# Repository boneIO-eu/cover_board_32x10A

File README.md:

# Cover Board 32x10A for 16 shutters (up/down)
This board is discontinued.
It is replaced by cover option in relay board 32x10A.

More info: http://docs.boneio.eu/

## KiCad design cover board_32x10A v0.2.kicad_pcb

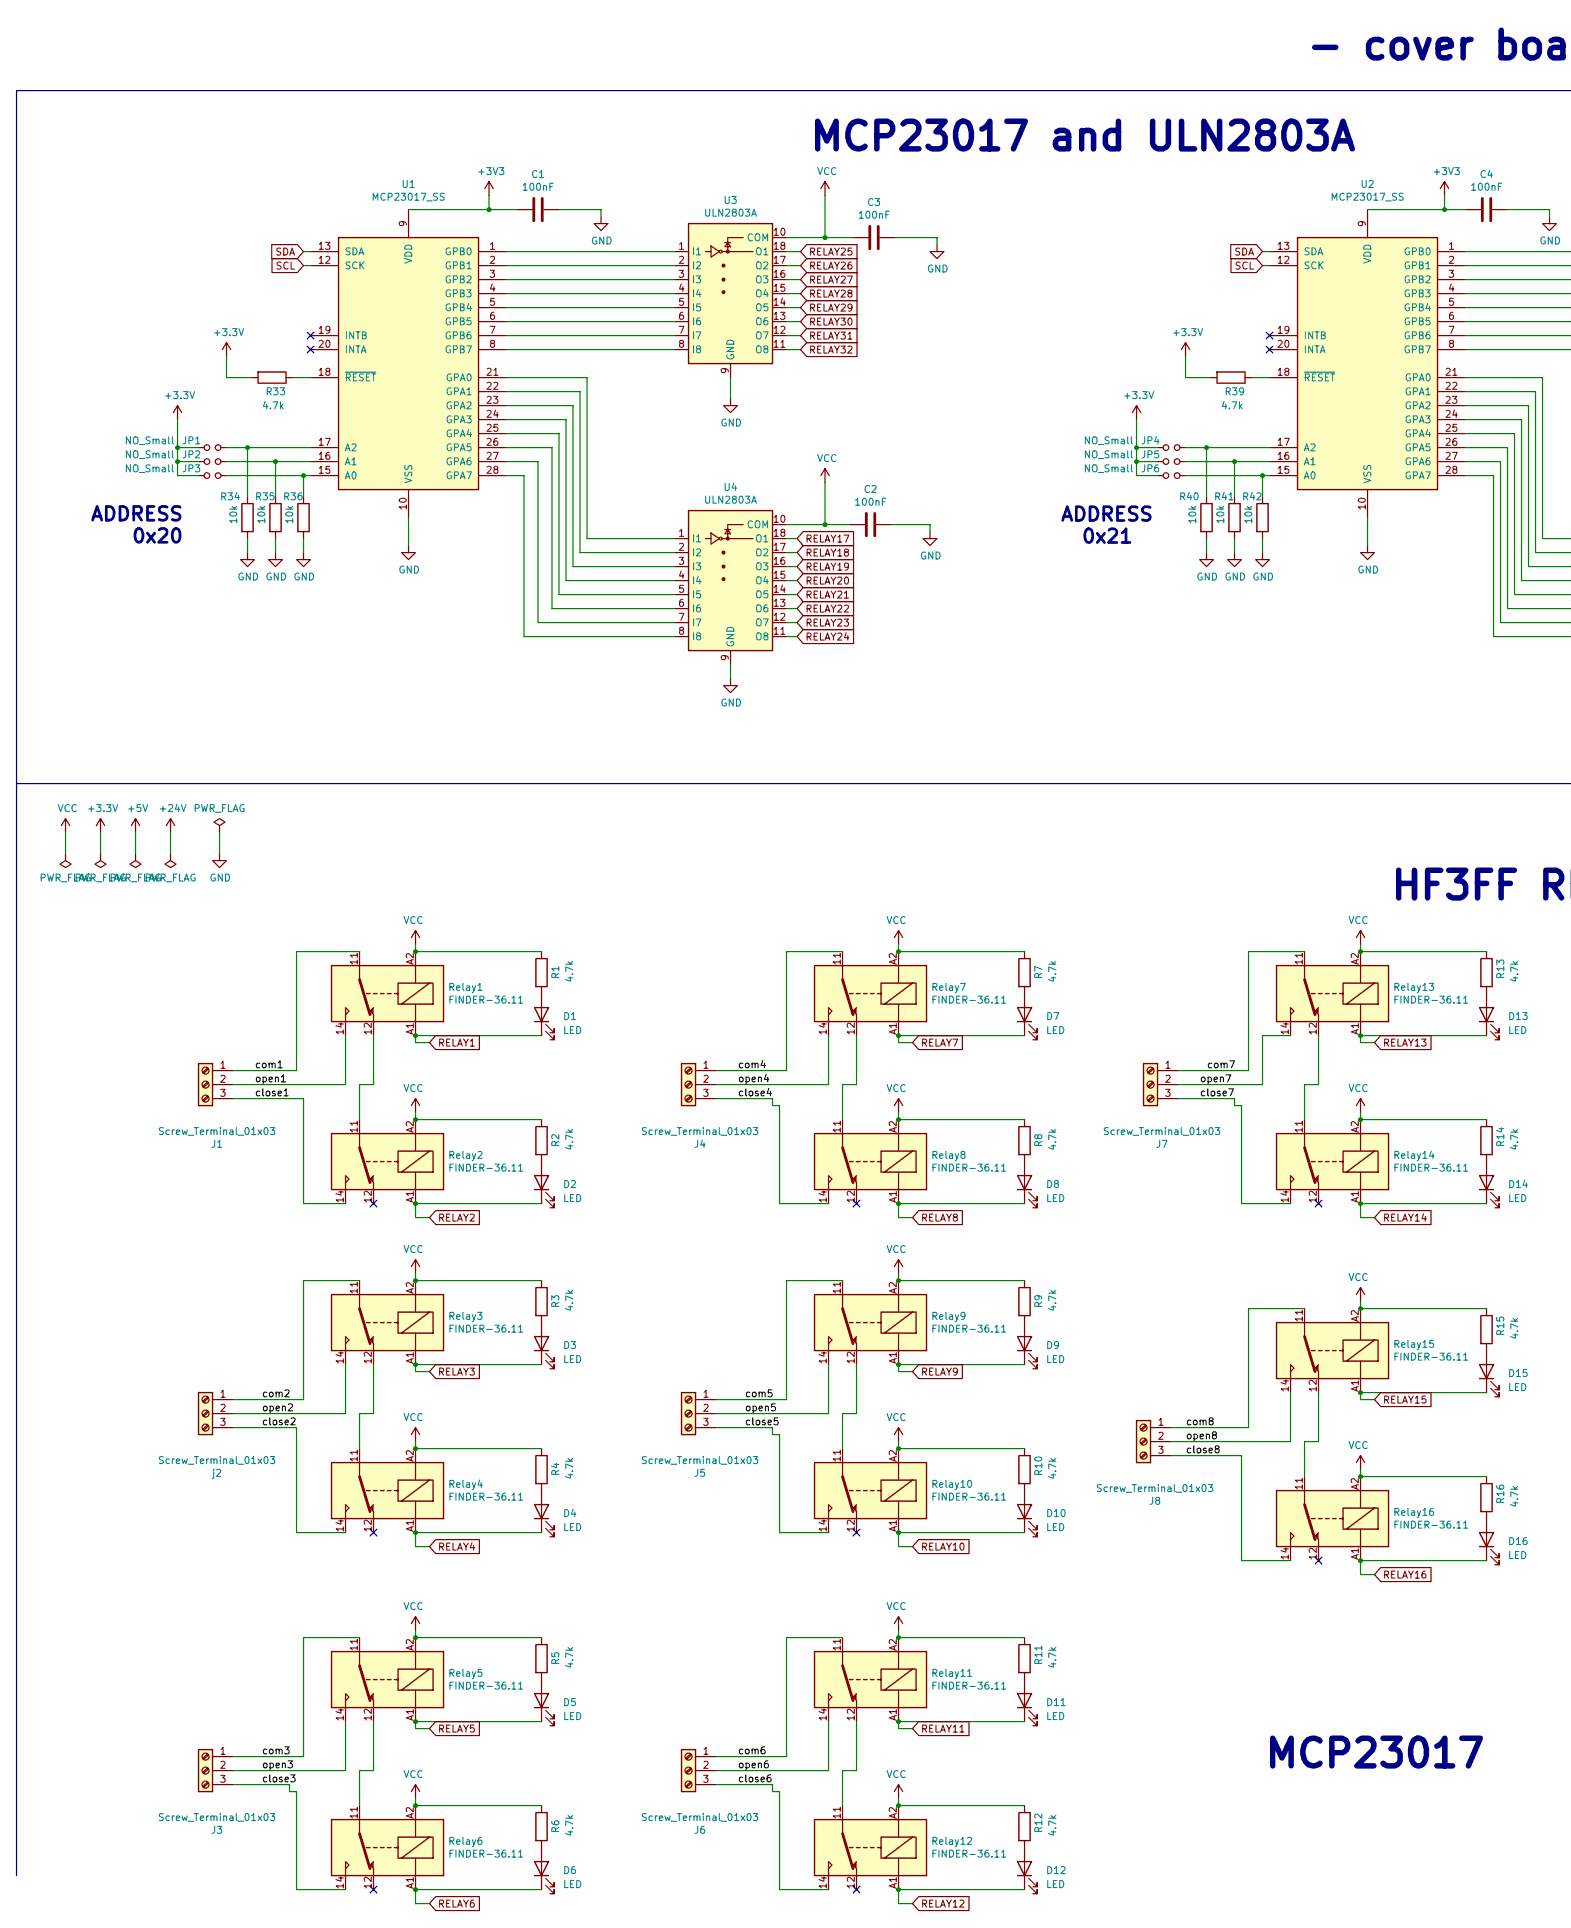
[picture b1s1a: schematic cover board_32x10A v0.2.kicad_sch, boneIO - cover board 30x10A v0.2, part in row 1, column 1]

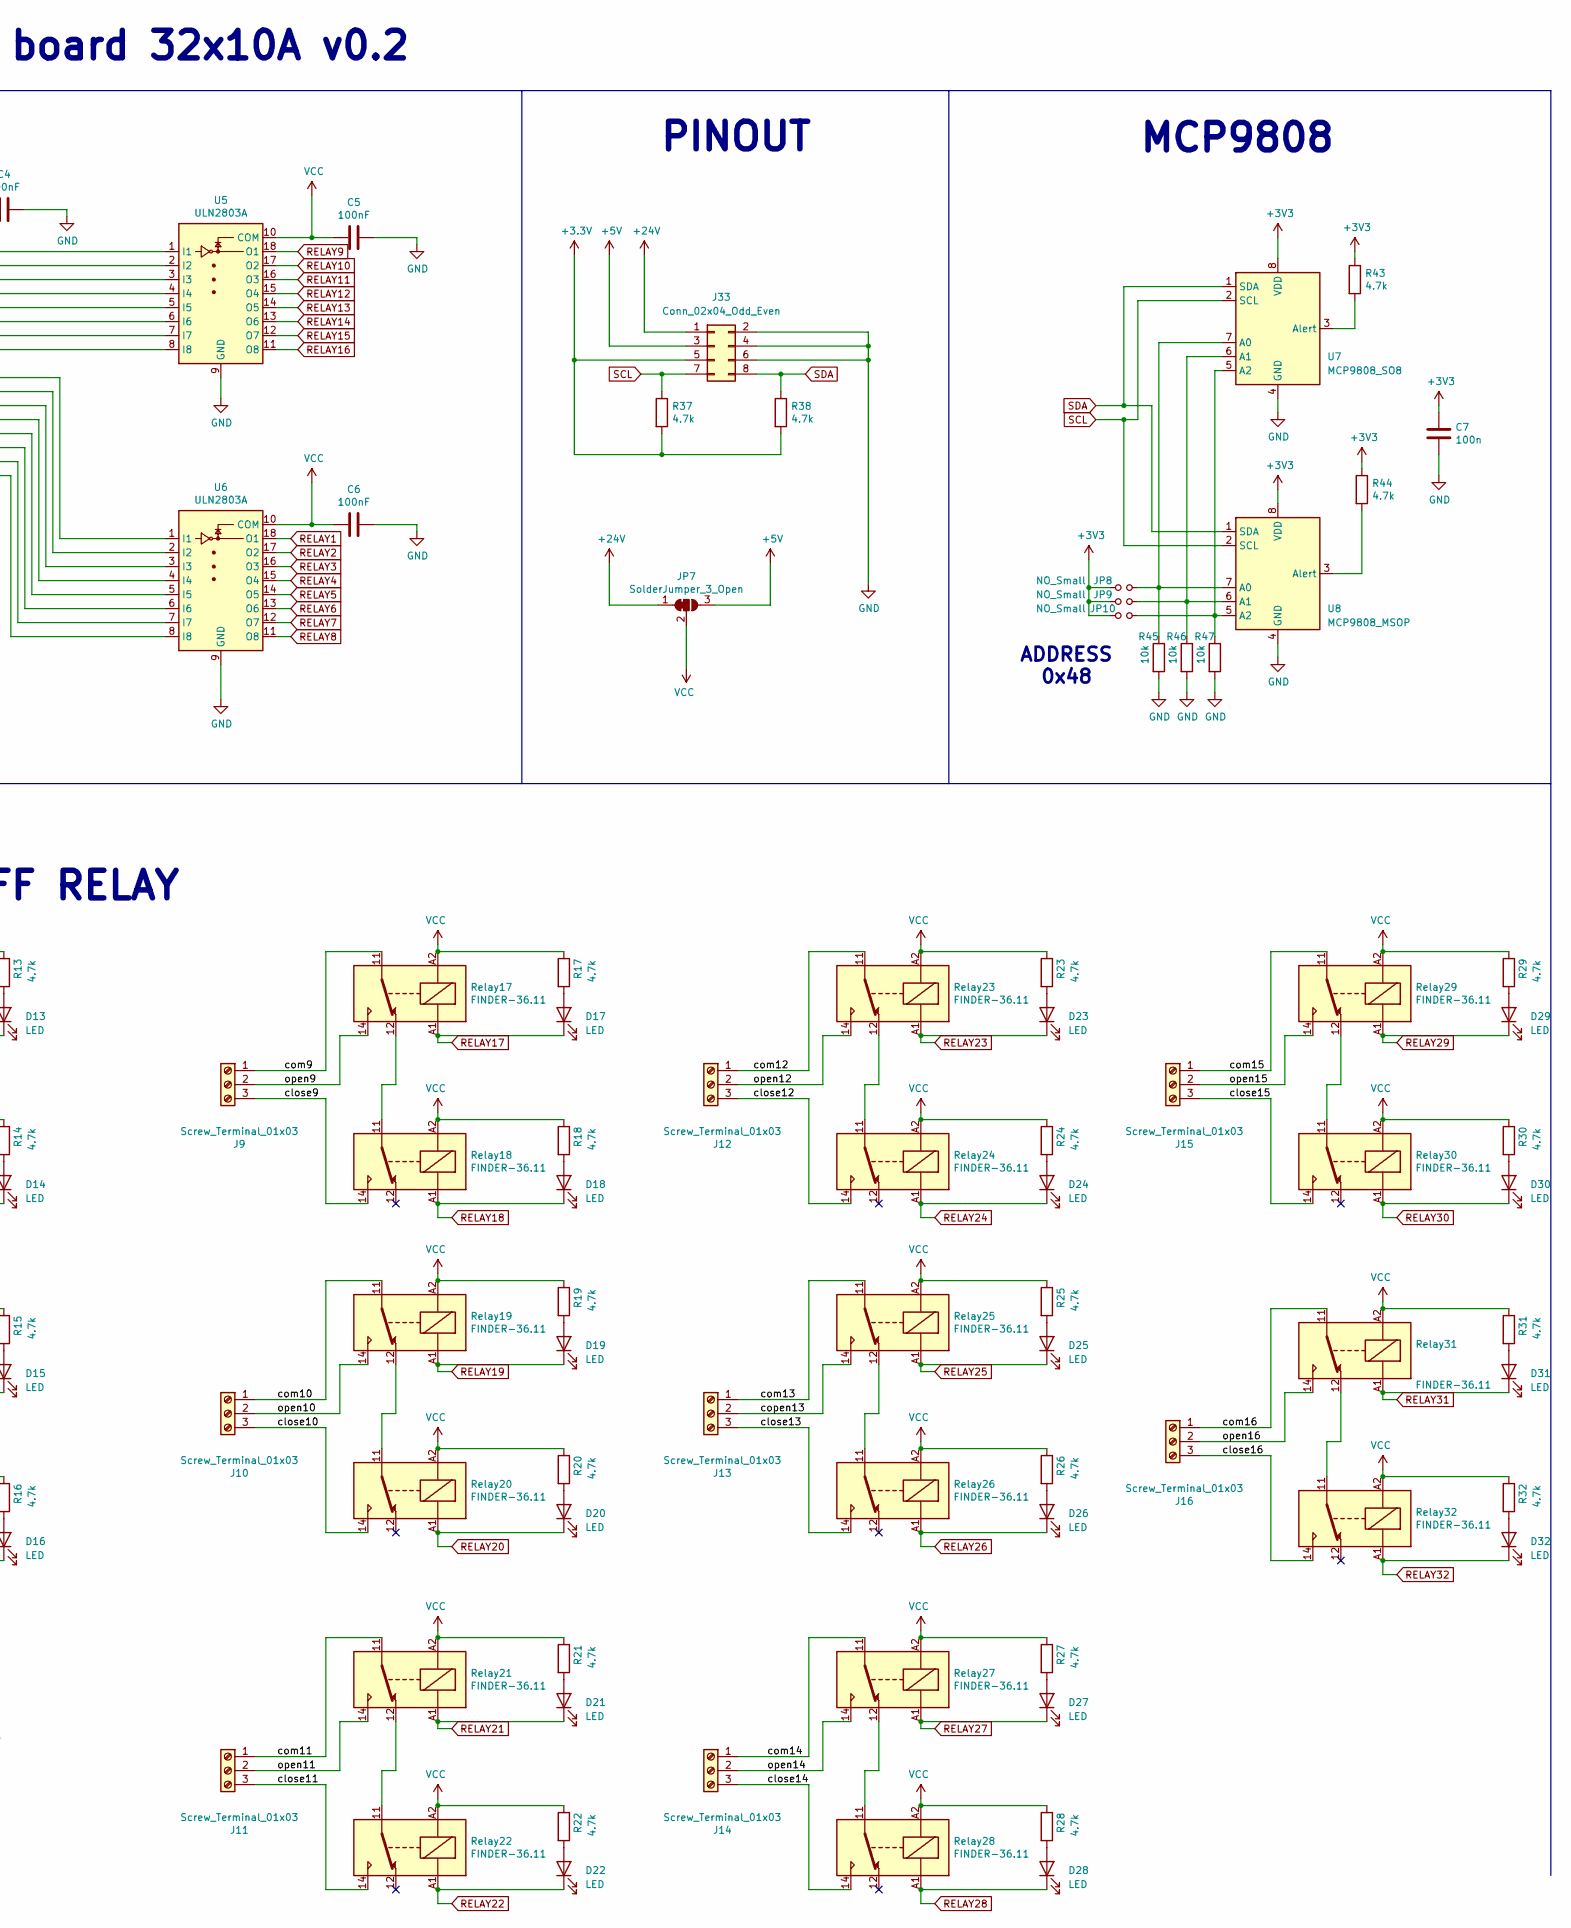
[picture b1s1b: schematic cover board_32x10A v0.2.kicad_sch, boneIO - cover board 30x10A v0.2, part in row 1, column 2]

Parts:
C1, C2, C3, C4, C5, C6: 100nF; C_0603_1608Metric
C7: 100n; C_0603_1608Metric
D1, D2, D3, D4, D5, D6, D7, D8, D9, D10, D11, D12, D13, D14, D15, D16, D17, D18, D19, D20, D21, D22, D23, D24, D25, D26, D27, D28, D29, D30, D31, D32: LED; LED_0603_1608Metric
J1, J3, J4, J5, J6, J7, J8, J9, J10, J11, J12, J13, J14, J15, J16: Screw_Terminal_01x03; PhoenixContact_GMSTBA_2,5_3-G_1x03_P7.50mm_Horizontal
J33: Conn_02x04_Odd_Even; PinHeader_2x04_P2.54mm_Vertical
JP1, JP2, JP3, JP4, JP5, JP6, JP8, JP9, JP10: NO_Small; SolderJumper-2_P1.3mm_Open_RoundedPad1.0x1.5mm
JP7: SolderJumper_3_Open; SolderJumper-3_P1.3mm_Bridged12_RoundedPad1.0x1.5mm
R1, R2, R3, R4, R5, R6, R7, R8, R9, R10, R11, R12, R13, R14, R15, R16, R17, R18, R19, R20, R21, R22, R23, R24, R25, R26, R27, R28, R29, R30, R31, R32, R33, R37, R38, R39, R43, R44: 4.7k; R_0603_1608Metric
R34, R35, R36, R40, R41, R42, R45, R46, R47: 10k; R_0603_1608Metric
Relay1, Relay2, Relay3, Relay4, Relay5, Relay6, Relay7, Relay8, Relay9, Relay10, Relay11, Relay12, Relay13, Relay14, Relay15, Relay16, Relay17, Relay18, Relay19, Relay20, Relay21, Relay22, Relay23, Relay24, Relay25, Relay26, Relay27, Relay28, Relay29, Relay30, Relay31, Relay32: FINDER-36.11; Relay_SPDT_Finder_36.11
U1, U2: MCP23017_SS; SSOP-28_5.3x10.2mm_P0.65mm
U3, U4, U5, U6: ULN2803A; SOIC-18W_7.5x11.6mm_P1.27mm
U7: MCP9808_SO8; SO-8_3.9x4.9mm_P1.27mm
U8: MCP9808_MSOP; MSOP-8_3x3mm_P0.65mm
j2: Screw_Terminal_01x03; PhoenixContact_GMSTBA_2,5_3-G_1x03_P7.50mm_Horizontal

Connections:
+5V: J33.3, JP7.3 (B)
+24V: J33.1, JP7.1 (A)
/close1: J1.3, Relay2.14
/close2: Relay4.14, j2.3
/close3: J3.3, Relay6.14
/close4: J4.3, Relay8.14
/close5: J5.3, Relay10.14
/close6: J6.3, Relay12.14
/close7: J7.3, Relay14.14
/close8: J8.3, Relay16.14
/close9: J9.3, Relay18.14
/close10: J10.3, Relay20.14
/close11: J11.3, Relay22.14
/close12: J12.3, Relay24.14
/close13: J13.3, Relay26.14
/close14: J14.3, Relay28.14
/close15: J15.3, Relay30.14
/close16: J16.3, Relay32.14
/com1: J1.1, Relay1.11
/com2: Relay3.11, j2.1
/com3: J3.1, Relay5.11
/com4: J4.1, Relay7.11
/com5: J5.1, Relay9.11
/com6: J6.1, Relay11.11
/com7: J7.1, Relay13.11
/com8: J8.1, Relay15.11
/com9: J9.1, Relay17.11
/com10: J10.1, Relay19.11
/com11: J11.1, Relay21.11
/com12: J12.1, Relay23.11
/com13: J13.1, Relay25.11
/com14: J14.1, Relay27.11
/com15: J15.1, Relay29.11
/com16: J16.1, Relay31.11
/copen13: J13.2, Relay25.14
/open1: J1.2, Relay1.14
/open2: Relay3.14, j2.2
/open3: J3.2, Relay5.14
/open4: J4.2, Relay7.14
/open5: J5.2, Relay9.14
/open6: J6.2, Relay11.14
/open7: J7.2, Relay13.14
/open8: J8.2, Relay15.14
/open9: J9.2, Relay17.14
/open10: J10.2, Relay19.14
/open11: J11.2, Relay21.14
/open12: J12.2, Relay23.14
/open14: J14.2, Relay27.14
/open15: J15.2, Relay29.14
/open16: J16.2, Relay31.14
GND: C1.1, C2.1, C3.1, C4.1, C5.1, C6.1, C7.2, J33.2, J33.4, J33.6, R34.2, R35.2, R36.2, R40.2, R41.2, R42.2, R45.2, R46.2, R47.2, U1.10 (VSS), U2.10 (VSS), U3.9 (GND), U4.9 (GND), U5.9 (GND), U6.9 (GND), U7.4 (GND), U8.4 (GND)
unnamed: D1.2 (A), R1.2
unnamed: D2.2 (A), R2.2
unnamed: D3.2 (A), R3.2
unnamed: D4.2 (A), R4.2
unnamed: D5.2 (A), R5.2
unnamed: D6.2 (A), R6.2
unnamed: D7.2 (A), R7.2
unnamed: D8.2 (A), R8.2
unnamed: D9.2 (A), R9.2
unnamed: D10.2 (A), R10.2
unnamed: D11.2 (A), R11.2
unnamed: D12.2 (A), R12.2
unnamed: D13.2 (A), R13.2
unnamed: D14.2 (A), R14.2
unnamed: D15.2 (A), R15.2
unnamed: D16.2 (A), R16.2
unnamed: D17.2 (A), R17.2
unnamed: D18.2 (A), R18.2
unnamed: D19.2 (A), R19.2
unnamed: D20.2 (A), R20.2
unnamed: D21.2 (A), R21.2
unnamed: D22.2 (A), R22.2
unnamed: D23.2 (A), R23.2
unnamed: D24.2 (A), R24.2
unnamed: D25.2 (A), R25.2
unnamed: D26.2 (A), R26.2
unnamed: D27.2 (A), R27.2
unnamed: D28.2 (A), R28.2
unnamed: D29.2 (A), R29.2
unnamed: D30.2 (A), R30.2
unnamed: D31.2 (A), R31.2
unnamed: D32.2 (A), R32.2
unnamed: JP1.2, R34.1, U1.17 (A2)
unnamed: JP2.2, R35.1, U1.16 (A1)
unnamed: JP3.2, R36.1, U1.15 (A0)
unnamed: JP4.2, R40.1, U2.17 (A2)
unnamed: JP5.2, R41.1, U2.16 (A1)
unnamed: JP6.2, R42.1, U2.15 (A0)
unnamed: JP8.2, R45.1, U7.7 (A0), U8.7 (A0)
unnamed: JP9.2, R46.1, U7.6 (A1), U8.6 (A1)
unnamed: JP10.2, R47.1, U7.5 (A2), U8.5 (A2)
unnamed: R33.1, U1.18 (~RESET)
unnamed: R39.1, U2.18 (~RESET)
unnamed: R43.2, U7.3 (Alert)
unnamed: R44.2, U8.3 (Alert)
unnamed: Relay1.12, Relay2.11
unnamed: Relay3.12, Relay4.11
unnamed: Relay5.12, Relay6.11
unnamed: Relay7.12, Relay8.11
unnamed: Relay9.12, Relay10.11
unnamed: Relay11.12, Relay12.11
unnamed: Relay13.12, Relay14.11
unnamed: Relay15.12, Relay16.11
unnamed: Relay17.12, Relay18.11
unnamed: Relay19.12, Relay20.11
unnamed: Relay21.12, Relay22.11
unnamed: Relay23.12, Relay24.11
unnamed: Relay25.12, Relay26.11
unnamed: Relay27.12, Relay28.11
unnamed: Relay29.12, Relay30.11
unnamed: Relay31.12, Relay32.11
unnamed: U1.1 (GPB0), U3.1 (I1)
unnamed: U1.2 (GPB1), U3.2 (I2)
unnamed: U1.3 (GPB2), U3.3 (I3)
unnamed: U1.4 (GPB3), U3.4 (I4)
unnamed: U1.5 (GPB4), U3.5 (I5)
unnamed: U1.6 (GPB5), U3.6 (I6)
unnamed: U1.7 (GPB6), U3.7 (I7)
unnamed: U1.8 (GPB7), U3.8 (I8)
unnamed: U1.21 (GPA0), U4.1 (I1)
unnamed: U1.22 (GPA1), U4.2 (I2)
unnamed: U1.23 (GPA2), U4.3 (I3)
unnamed: U1.24 (GPA3), U4.4 (I4)
unnamed: U1.25 (GPA4), U4.5 (I5)
unnamed: U1.26 (GPA5), U4.6 (I6)
unnamed: U1.27 (GPA6), U4.7 (I7)
unnamed: U1.28 (GPA7), U4.8 (I8)
unnamed: U2.1 (GPB0), U5.1 (I1)
unnamed: U2.2 (GPB1), U5.2 (I2)
unnamed: U2.3 (GPB2), U5.3 (I3)
unnamed: U2.4 (GPB3), U5.4 (I4)
unnamed: U2.5 (GPB4), U5.5 (I5)
unnamed: U2.6 (GPB5), U5.6 (I6)
unnamed: U2.7 (GPB6), U5.7 (I7)
unnamed: U2.8 (GPB7), U5.8 (I8)
unnamed: U2.21 (GPA0), U6.1 (I1)
unnamed: U2.22 (GPA1), U6.2 (I2)
unnamed: U2.23 (GPA2), U6.3 (I3)
unnamed: U2.24 (GPA3), U6.4 (I4)
unnamed: U2.25 (GPA4), U6.5 (I5)
unnamed: U2.26 (GPA5), U6.6 (I6)
unnamed: U2.27 (GPA6), U6.7 (I7)
unnamed: U2.28 (GPA7), U6.8 (I8)
RELAY1: D1.1 (K), Relay1.A1, U6.18 (O1)
RELAY2: D2.1 (K), Relay2.A1, U6.17 (O2)
RELAY3: D3.1 (K), Relay3.A1, U6.16 (O3)
RELAY4: D4.1 (K), Relay4.A1, U6.15 (O4)
RELAY5: D5.1 (K), Relay5.A1, U6.14 (O5)
RELAY6: D6.1 (K), Relay6.A1, U6.13 (O6)
RELAY7: D7.1 (K), Relay7.A1, U6.12 (O7)
RELAY8: D8.1 (K), Relay8.A1, U6.11 (O8)
RELAY9: D9.1 (K), Relay9.A1, U5.18 (O1)
RELAY10: D10.1 (K), Relay10.A1, U5.17 (O2)
RELAY11: D11.1 (K), Relay11.A1, U5.16 (O3)
RELAY12: D12.1 (K), Relay12.A1, U5.15 (O4)
RELAY13: D13.1 (K), Relay13.A1, U5.14 (O5)
RELAY14: D14.1 (K), Relay14.A1, U5.13 (O6)
RELAY15: D15.1 (K), Relay15.A1, U5.12 (O7)
RELAY16: D16.1 (K), Relay16.A1, U5.11 (O8)
RELAY17: D17.1 (K), Relay17.A1, U4.18 (O1)
RELAY18: D18.1 (K), Relay18.A1, U4.17 (O2)
RELAY19: D19.1 (K), Relay19.A1, U4.16 (O3)
RELAY20: D20.1 (K), Relay20.A1, U4.15 (O4)
RELAY21: D21.1 (K), Relay21.A1, U4.14 (O5)
RELAY22: D22.1 (K), Relay22.A1, U4.13 (O6)
RELAY23: D23.1 (K), Relay23.A1, U4.12 (O7)
RELAY24: D24.1 (K), Relay24.A1, U4.11 (O8)
RELAY25: D25.1 (K), Relay25.A1, U3.18 (O1)
RELAY26: D26.1 (K), Relay26.A1, U3.17 (O2)
RELAY27: D27.1 (K), Relay27.A1, U3.16 (O3)
RELAY28: D28.1 (K), Relay28.A1, U3.15 (O4)
RELAY29: D29.1 (K), Relay29.A1, U3.14 (O5)
RELAY30: D30.1 (K), Relay30.A1, U3.13 (O6)
RELAY31: D31.1 (K), Relay31.A1, U3.12 (O7)
RELAY32: D32.1 (K), Relay32.A1, U3.11 (O8)
SCL: J33.7, R37.1, U1.12 (SCK), U2.12 (SCK), U7.2 (SCL), U8.2 (SCL)
SDA: J33.8, R38.1, U1.13 (SDA), U2.13 (SDA), U7.1 (SDA), U8.1 (SDA)
VCC: C2.2, C3.2, C5.2, C6.2, JP7.2 (C), R1.1, R2.1, R3.1, R4.1, R5.1, R6.1, R7.1, R8.1, R9.1, R10.1, R11.1, R12.1, R13.1, R14.1, R15.1, R16.1, R17.1, R18.1, R19.1, R20.1, R21.1, R22.1, R23.1, R24.1, R25.1, R26.1, R27.1, R28.1, R29.1, R30.1, R31.1, R32.1, Relay1.A2, Relay2.A2, Relay3.A2, Relay4.A2, Relay5.A2, Relay6.A2, Relay7.A2, Relay8.A2, Relay9.A2, Relay10.A2, Relay11.A2, Relay12.A2, Relay13.A2, Relay14.A2, Relay15.A2, Relay16.A2, Relay17.A2, Relay18.A2, Relay19.A2, Relay20.A2, Relay21.A2, Relay22.A2, Relay23.A2, Relay24.A2, Relay25.A2, Relay26.A2, Relay27.A2, Relay28.A2, Relay29.A2, Relay30.A2, Relay31.A2, Relay32.A2, U3.10 (COM), U4.10 (COM), U5.10 (COM), U6.10 (COM)

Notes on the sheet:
ADDRESS 0x48
HF3FF RELAY
ADDRESS 0x20
MCP23017
ADDRESS 0x21
MCP9808
MCP23017 and ULN2803A
- cover board 32x10A v0.2
PINOUT

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
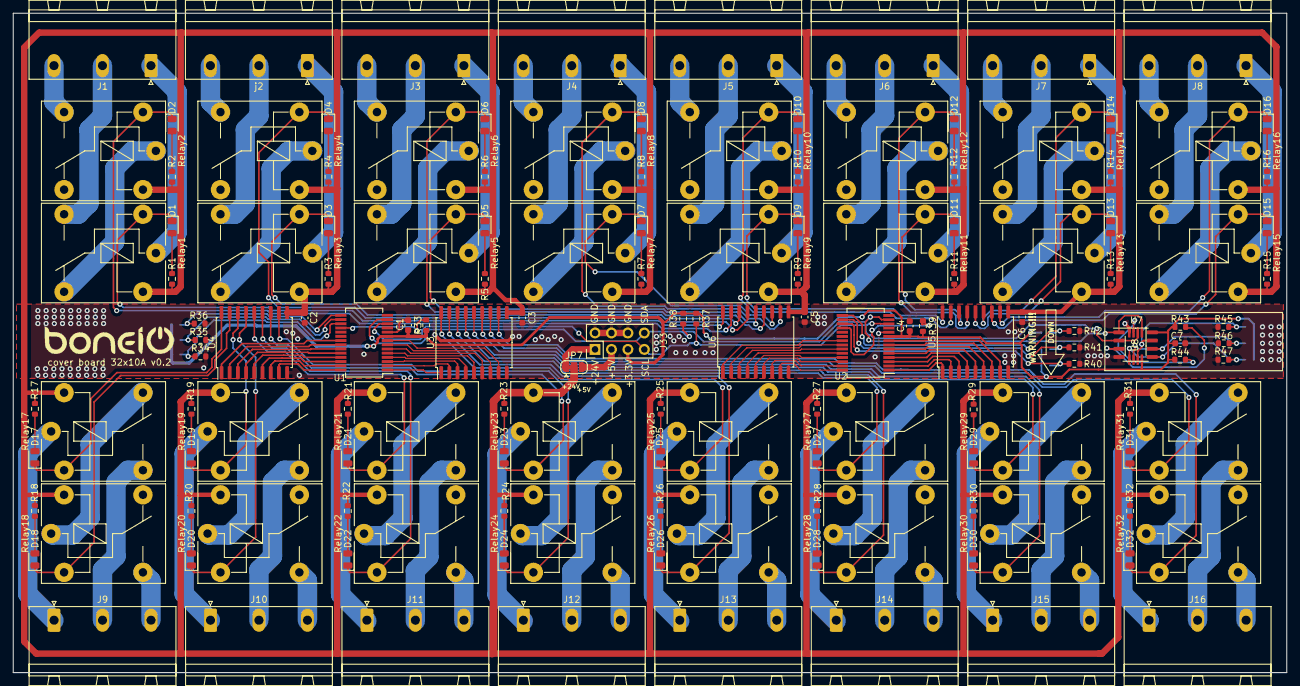
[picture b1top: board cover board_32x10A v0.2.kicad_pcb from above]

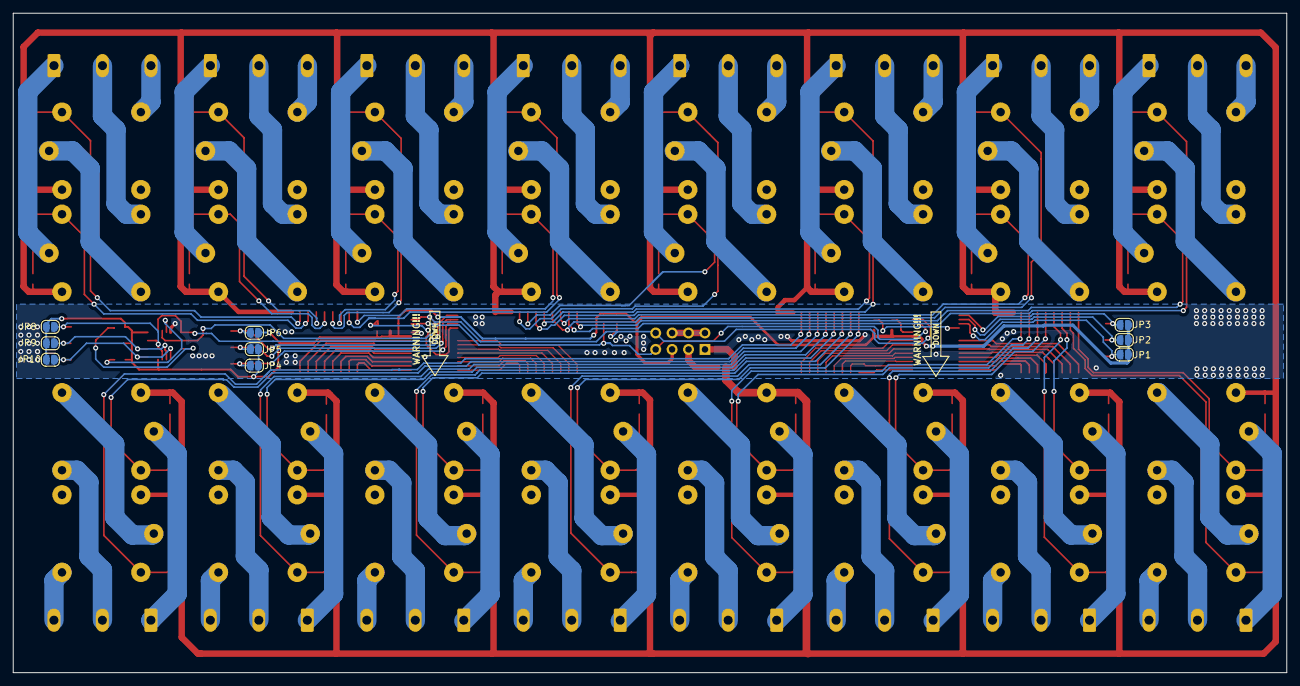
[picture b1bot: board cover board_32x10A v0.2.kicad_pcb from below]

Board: 2 copper layers, 197.0 x 102.0 mm, 153 parts (9 on the bottom side), 180 nets.

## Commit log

2021-12-19 boneIO - shutter board 32x10A
2021-12-19 Added no connection flags to schema
2022-01-17 Directory cleanup
2022-01-17 Create LICENSE
2022-01-19 Added photo of the board
2022-01-19 Added readme file
2022-03-08 v0.2
